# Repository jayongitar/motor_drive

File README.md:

"# motor_drive" 
"# motor_drive"

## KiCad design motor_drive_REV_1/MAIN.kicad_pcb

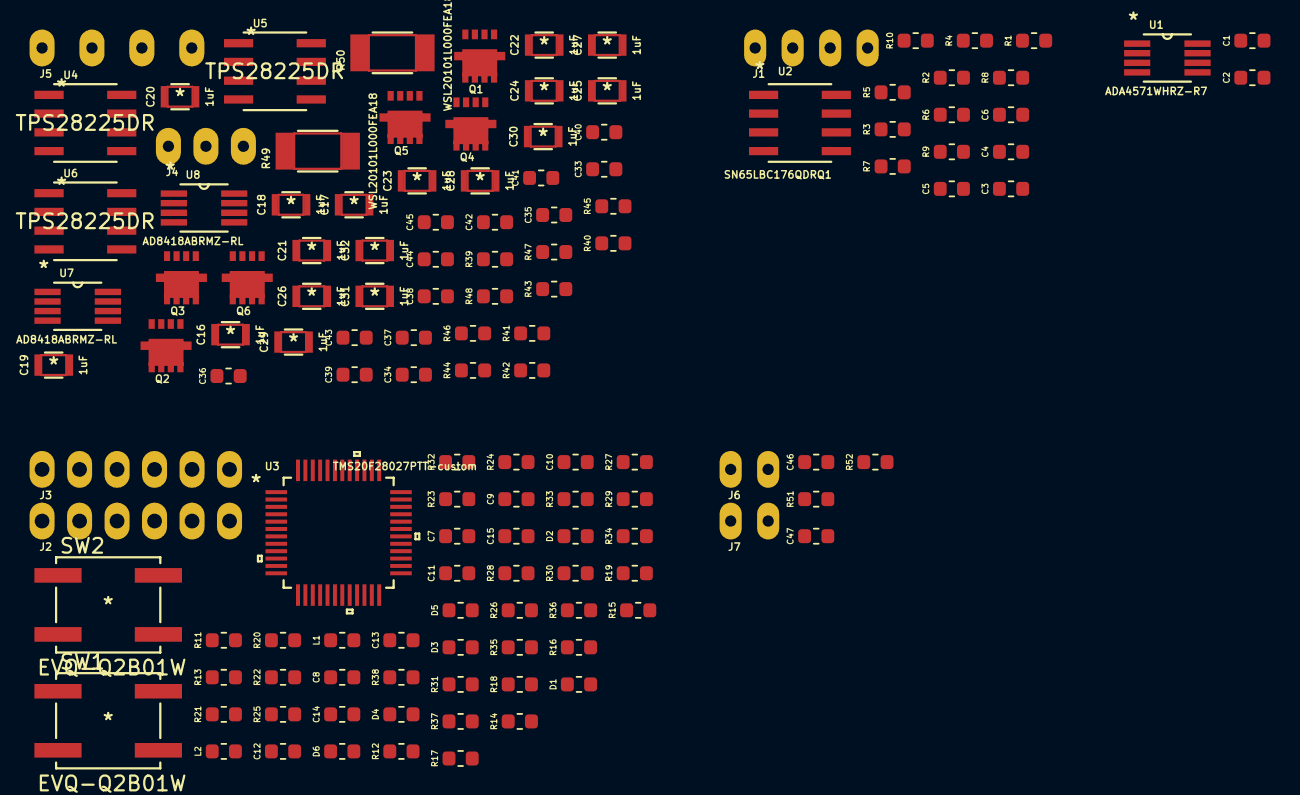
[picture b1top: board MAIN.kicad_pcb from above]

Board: 2 copper layers, 130 parts (0 on the bottom side), 81 nets, no tracks yet.

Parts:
C1, C6, C7, C8: 2.2uF; C_0603_1608Metric
C2, C5, C9, C10, C44, C45: 0.01uF; C_0603_1608Metric
C3, C4: 680pF; C_0603_1608Metric
C11, C14: 4.7uF; C_0603_1608Metric
C12, C15, C42, C43: 1uF; C_0603_1608Metric
C13: 100pF; C_0603_1608Metric
C16, C17, C18, C19, C20, C21, C22, C23, C24, C25, C26, C27, C28, C29, C30, C31, C32: 1uF; gen_0805
C33, C34, C35, C36, C37, C38, C39, C40, C41, C46, C47: C; C_0603_1608Metric
D1, D2, D3, D4, D5, D6: LED; C_0603_1608Metric
J1: Conn_01x04; 4pos_254
J2, J3: Conn_01x06; 6pos_254
J4: Conn_01x03; 3pos_254
J5: Conn_01x04; 4pos_338
J6, J7: Conn_01x02; 2pos_254
L1, L2: 2.2uF; C_0603_1608Metric
Q1, Q2, Q3, Q4, Q5, Q6: nmos; NTTGS5820NL-D
R1, R2, R6, R7, R8, R21, R31, R32, R33, R34, R35, R36, R37, R38: 375; C_0603_1608Metric
R3, R5: 680; C_0603_1608Metric
R4: 120; C_0603_1608Metric
R9: NP; C_0603_1608Metric
R10, R19, R20: 4.7k; C_0603_1608Metric
R11, R12, R13, R14, R15, R16, R17, R18, R23, R24, R25, R26, R27, R28, R29, R30: 10k; C_0603_1608Metric
R22: 2.2k; C_0603_1608Metric
R39, R40, R41, R42, R51, R52: R; C_0603_1608Metric
R43, R44, R45, R46, R47, R48: 10; C_0603_1608Metric
R49, R50: WSL20101L000FEA18
SW1, SW2: EVQ-Q2B01W
U1: ADA4571WHRZ-R7; AD8418ABRMZ-RL
U2: SN65LBC176QDRQ1
U3: TMS20F28027PTT-custom; TMS320F28027PTT
U4, U5, U6: TPS28225DR
U7, U8: AD8418ABRMZ-RL

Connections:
/5.0V: C1.1, C2.1, C4.2, C5.2, C6.2, C7.1, C8.1, C9.1, C10.1, C11.1, C15.1, D1.2, D2.2, D3.2, D4.2, D5.2, D6.2, J2.5, J6.1, J7.1, L1.2, L2.1, R5.2, R9.1, R11.1, R12.1, R22.2, R23.2, R24.2, R25.2, R26.2, R27.2, R28.2, R29.2, R30.2, U1.7, U2.8, U3.32, U3.44
/7.5V: C33.2, C34.2, C35.2, C39.2, C40.2, C41.2, C42.2, C43.2, C44.2, C45.2, R40.2, R41.2, R42.2, U4.6, U5.6, U6.6, U7.6, U7.7, U8.6, U8.7
/CLK: J2.4, R35.2
/DEnRE: R9.2, R10.1, U2.2, U2.3, U3.47
/F28027/BUTTON_0: R11.2, SW1.1, U3.41
/F28027/BUTTON_1: R12.2, SW2.1, U3.42
/F28027/JTAG_TCK: J3.1, R32.2
/F28027/JTAG_TDI: J3.4, R38.2
/F28027/JTAG_TDO: J3.2, R34.2
/F28027/JTAG_TMS: J3.3, R36.2
/F28027/JTAG_nTRST: J3.5, R21.2
/F28027/LED_0: R13.2, U3.31
/F28027/LED_1: R14.2, U3.36
/F28027/LED_2: R15.2, U3.19
/F28027/LED_3: R16.2, U3.38
/F28027/LED_4: R17.2, U3.39
/F28027/LED_5: R18.2, U3.40
/GND: C1.2, C2.2, C3.1, C5.1, C6.1, C7.2, C8.2, C9.2, C10.2, C11.2, C12.2, C13.1, C14.2, C15.2, C33.1, C34.1, C35.1, C39.1, C40.1, C41.1, C42.1, C43.1, C44.1, C45.1, C46.2, C47.2, J1.1, J2.6, J3.6, R3.1, R6.1, R10.2, R19.1, R20.1, R39.2, R51.2, R52.2, SW1.4, SW2.4, U1.1, U1.3, U1.6, U1.8, U2.5, U3.12, U3.33, U3.43, U4.4, U5.4, U6.4, U7.2, U7.3, U8.2, U8.3
/I_sense_1: U3.4, U3.13, U8.5
/I_sense_2: U3.5, U3.14
/MISO: J2.2, R33.2
/MOSI: J2.1, R31.2
/RS422/A: J1.4, R1.2
/RS422/B: J1.3, R2.2
/RS422/balance: J1.2, R6.2
/UART_RX: R8.1, U3.48
/UART_TX: R7.1, U3.1
/chip_reset: C13.2, R22.1, U3.3
/cos: U1.2, U3.7, U3.18
/nEN: J2.3, R37.2
/power/DC_neg: C16.2, C17.2, C18.2, C20.2, C21.2, C22.2, C23.2, C24.2, C25.2, C26.2, C27.2, C28.2, C29.2, C30.2, C31.2, C32.2, J4.2, Q2.3, Q4.3, Q6.3, R39.1
/power/DC_pos: C16.1, C17.1, C18.1, C19.1, C21.1, C22.1, C23.1, C24.1, C25.1, C26.1, C27.1, C28.1, C29.1, C30.1, C31.1, C32.1, J4.1, Q1.1, Q3.1, Q5.1
/power/GH_0: R43.2, U4.1
/power/GH_1: R45.2, U5.1
/power/GH_2: R47.2, U6.1
/power/GL_0: R44.2, U4.5
/power/GL_1: R46.2, U5.5
/power/GL_2: R48.2, U6.5
/power/SW_0: C36.2, Q1.3, Q2.1, R50.2, U4.8, U7.1
/power/SW_1: C37.2, Q3.3, Q4.1, R49.2, U5.8, U8.1
/power/SW_2: C38.2, J5.3, Q5.3, Q6.1, U6.8
/power/U: J5.1, R50.1, U7.8
/power/V: J5.2, R49.1, U8.8
/power/shield: C19.2, C20.1, J4.3, J5.4
/sin: U1.4, U3.6, U3.17
/therm_0: C46.1, J6.2, R51.1
/therm_1: C47.1, J7.2, R52.1, U3.15
unnamed: C3.2, R1.1, R3.2, R4.2, U2.6
unnamed: C4.1, R2.1, R4.1, R5.1, U2.7
unnamed: C12.1, L1.1, U3.35
unnamed: C14.1, L2.2, U3.11
unnamed: C36.1, U4.2
unnamed: C37.1, U5.2
unnamed: C38.1, U6.2
unnamed: D1.1, R13.1
unnamed: D2.1, R14.1
unnamed: D3.1, R15.1
unnamed: D4.1, R16.1
unnamed: D5.1, R17.1
unnamed: D6.1, R18.1
unnamed: Q1.2, R43.1
unnamed: Q2.2, R44.1
unnamed: Q3.2, R45.1
unnamed: Q4.2, R46.1
unnamed: Q5.2, R47.1
unnamed: Q6.2, R48.1
unnamed: R7.2, U2.4
unnamed: R8.2, U2.1
unnamed: R19.2, R21.1, U3.2
unnamed: R20.2, U3.34
unnamed: R23.1, R37.1, U3.24
unnamed: R24.1, R38.1, U3.20
unnamed: R25.1, R35.1, U3.25
unnamed: R26.1, R36.1, U3.21
unnamed: R27.1, R33.1, U3.26
unnamed: R28.1, R34.1, U3.22
unnamed: R29.1, R31.1, U3.27
unnamed: R30.1, R32.1, U3.23
unnamed: R40.1, U4.7
unnamed: R41.1, U5.7
unnamed: R42.1, U6.7

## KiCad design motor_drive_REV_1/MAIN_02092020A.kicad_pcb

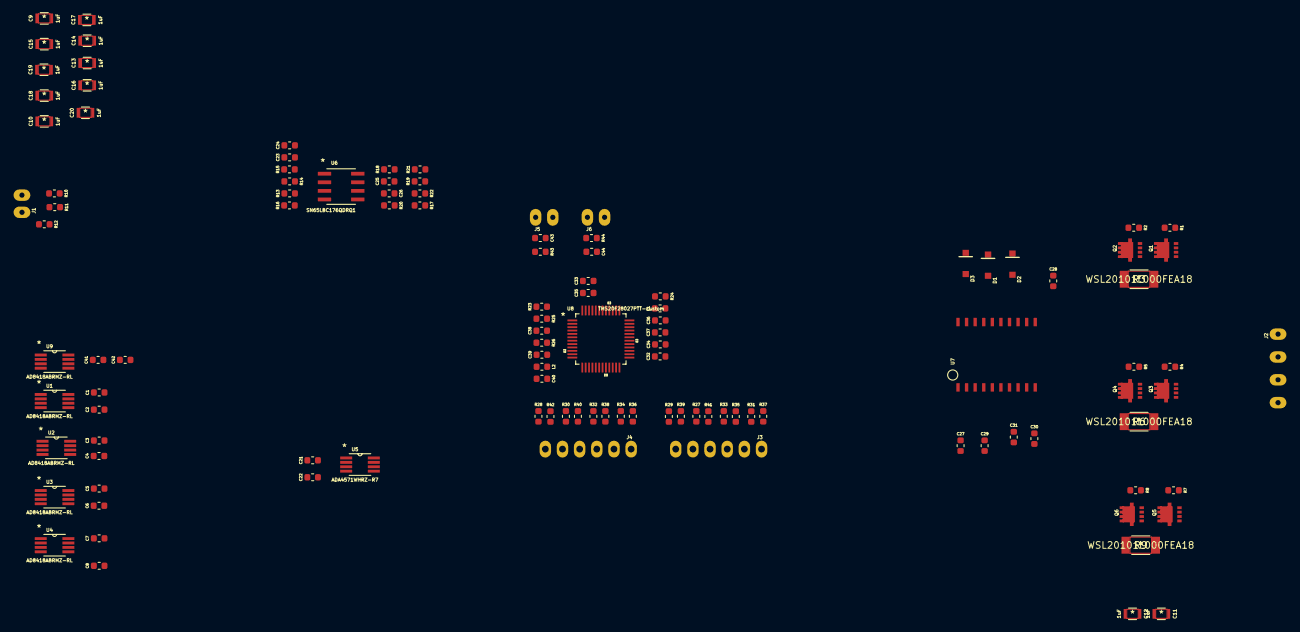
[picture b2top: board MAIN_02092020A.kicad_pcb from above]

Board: 2 copper layers, 114 parts (0 on the bottom side), 74 nets, no tracks yet.

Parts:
C1, C3, C5, C7, C37, C40, C41: 1uF; C_0603_1608Metric
C2, C4, C6, C8, C22, C24, C28, C34, C35, C42: 0.01uF; C_0603_1608Metric
C9, C10, C11, C12, C13, C14, C15, C16, C17, C18, C19, C20: 1uF; gen_0805
C21, C23, C27, C32, C33: 2.2uF; C_0603_1608Metric
C25, C26: 680pF; C_0603_1608Metric
C29, C30, C31: 0.22uF; C_0603_1608Metric
C36, C39: 4.7uF; C_0603_1608Metric
C38: 100pF; C_0603_1608Metric
C43, C44: C; C_0603_1608Metric
D1, D2, D3: D; SOD123
J1, J5, J6: Conn_01x02; 2pos_254
J2: Conn_01x04; 4pos_338
J3, J4: Conn_01x06; 6pos_254
L1, L2: 2.2uF; C_0603_1608Metric
Q1, Q2, Q3, Q4, Q5, Q6: nmos; NTTGS5820NL-D
R1, R2, R4, R5, R7, R8: 10; C_0603_1608Metric
R3, R6, R9: WSL20101L000FEA18
R10, R11, R12, R23, R43, R44: R; C_0603_1608Metric
R13: NP; C_0603_1608Metric
R14, R24: 4.7k; C_0603_1608Metric
R15, R16, R17, R21, R22, R25, R35, R36, R37, R38, R39, R40, R41, R42: 375; C_0603_1608Metric
R18, R20: 680; C_0603_1608Metric
R19: 120; C_0603_1608Metric
R26: 2.2k; C_0603_1608Metric
R27, R28, R29, R30, R31, R32, R33, R34: 10k; C_0603_1608Metric
U1, U2, U3, U4, U9: AD8418ABRMZ-RL
U5: ADA4571WHRZ-R7; AD8418ABRMZ-RL
U6: SN65LBC176QDRQ1
U7: FAN7888_gen; FAN7888
U8: TMS20F28027PTT-custom; TMS320F28027PTT

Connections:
/5.0V: C1.2, C2.2, C3.2, C4.2, C5.2, C6.2, C7.2, C8.2, C21.1, C23.1, C24.1, C25.2, C27.1, C28.1, C32.1, C33.1, C34.1, C35.1, C36.1, C40.1, C41.2, C42.2, D1.2, D2.2, D3.2, J3.5, J5.1, J6.1, L1.2, L2.1, R13.1, R18.2, R26.2, R27.2, R28.2, R29.2, R30.2, R31.2, R32.2, R33.2, R34.2, U1.6, U1.7, U2.6, U2.7, U3.6, U3.7, U4.6, U4.7, U5.7, U6.8, U7.12, U8.32, U8.44, U9.6, U9.7
/CLK: J3.4, R39.2
/DC_Link_Input/5.0V: C9.1, C10.1, C13.1, C14.1, C15.1, C16.1, C17.1, C18.1, C19.1, C20.1
/DC_Link_Input/GND: C9.2, C10.2, C13.2, C14.2, C15.2, C16.2, C17.2, C18.2, C19.2, C20.2
/DC_neg: C12.2, J1.1, Q2.3, Q4.3, Q6.3, R12.2, U4.1
/DC_pos: C11.1, Q1.1, Q3.1, Q5.1, R10.1, R11.1, U3.1
/DEnRE: R13.2, R14.1, U6.2, U6.3, U8.47
/F28027/JTAG_TCK: J4.1, R36.2
/F28027/JTAG_TDI: J4.4, R42.2
/F28027/JTAG_TDO: J4.2, R38.2
/F28027/JTAG_TMS: J4.3, R40.2
/F28027/JTAG_nTRST: J4.5, R25.2
/GH_1: R1.2, U7.19
/GH_2: R4.2, U7.15
/GH_3: R7.2, U7.9
/GL_1: R2.2, U7.17
/GL_2: R5.2, U7.13
/GL_3: R8.2, U7.7
/GND: C1.1, C2.1, C3.1, C4.1, C5.1, C6.1, C7.1, C8.1, C21.2, C23.2, C24.2, C26.1, C27.2, C28.2, C32.2, C33.2, C34.2, C35.2, C36.2, C37.2, C38.1, C39.2, C40.2, C41.1, C42.1, C43.2, C44.2, J3.6, J4.6, R14.2, R17.1, R20.1, R23.1, R24.1, R43.2, R44.2, U1.2, U1.3, U2.2, U2.3, U3.2, U3.3, U4.2, U4.3, U5.1, U5.3, U5.6, U5.8, U6.5, U7.11, U8.12, U8.33, U8.43, U9.2, U9.3
/HS_1: U7.1, U8.28
/HS_2: U7.3, U8.37
/HS_3: U7.5, U8.39
/IDC_sense: U3.5, U8.7
/IDC_sense_p: J1.2, R10.2, U3.8
/I_sense_1: U8.4, U8.13, U9.5
/I_sense_2: U1.5, U8.5, U8.14
/I_sense_3: U2.5, U8.6
/I_sense_n1: J2.1, R3.1
/I_sense_n2: J2.2, R6.1
/I_sense_n3: J2.3, R9.1
/I_sense_p1: C29.2, Q1.3, Q2.1, R3.2, U7.18
/I_sense_p2: C30.2, Q3.3, Q4.1, R6.2, U7.14
/I_sense_p3: C31.2, Q5.3, Q6.1, R9.2, U7.8
/LS_1: U7.2, U8.29
/LS_2: U7.4, U8.38
/LS_3: U7.6, U8.40
/MISO: J3.1, R37.2
/MOSI: J3.2, R35.2
/UART_RX: R15.1, U8.48
/UART_TX: R16.1, U8.1
/VDC_sense: U4.5, U8.8
/VDC_sense_p: R11.2, R12.1, U4.8
/chip_reset: C38.2, R26.1, U8.3
/cos: U5.2, U8.10, U8.18
/nEN: J3.3, R41.2
/phase_shield: C11.2, C12.1, J2.4
/sin: U5.4, U8.9, U8.17
/therm_1: C43.1, J5.2, R43.1, U8.15
/therm_2: C44.1, J6.2, R44.1, U8.16
unnamed: C25.1, R18.1, R19.1, R21.1, U6.7
unnamed: C26.2, R19.2, R20.2, R22.1, U6.6
unnamed: C29.1, D1.1, U7.20
unnamed: C30.1, D2.1, U7.16
unnamed: C31.1, D3.1, U7.10
unnamed: C37.1, L1.1, U8.35
unnamed: C39.1, L2.2, U8.11
unnamed: Q1.2, R1.1
unnamed: Q2.2, R2.1
unnamed: Q3.2, R4.1
unnamed: Q4.2, R5.1
unnamed: Q5.2, R7.1
unnamed: Q6.2, R8.1
unnamed: R15.2, U6.1
unnamed: R16.2, U6.4
unnamed: R23.2, R25.1, U8.2
unnamed: R24.2, U8.34
unnamed: R27.1, R41.1, U8.24
unnamed: R28.1, R42.1, U8.20
unnamed: R29.1, R39.1, U8.25
unnamed: R30.1, R40.1, U8.21
unnamed: R31.1, R37.1, U8.26
unnamed: R32.1, R38.1, U8.22
unnamed: R33.1, R35.1, U8.27
unnamed: R34.1, R36.1, U8.23

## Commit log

2020-01-19 added KiCad files
2020-01-28 work on component libraries and schematic
2020-02-05 organizing pinout and BOM
2020-02-05 piccolo pinout
2020-02-09 working on adding thermistors but encountered too many hierarchicaly copies bug
2020-02-10 started layout
2020-02-10 layout
2020-02-20 gate drive rework and schematic re-organization
2020-02-29 second try at layout

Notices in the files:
parts and their libraries:
Copyright 2016 Accelerated Designs. All rights reserved.
